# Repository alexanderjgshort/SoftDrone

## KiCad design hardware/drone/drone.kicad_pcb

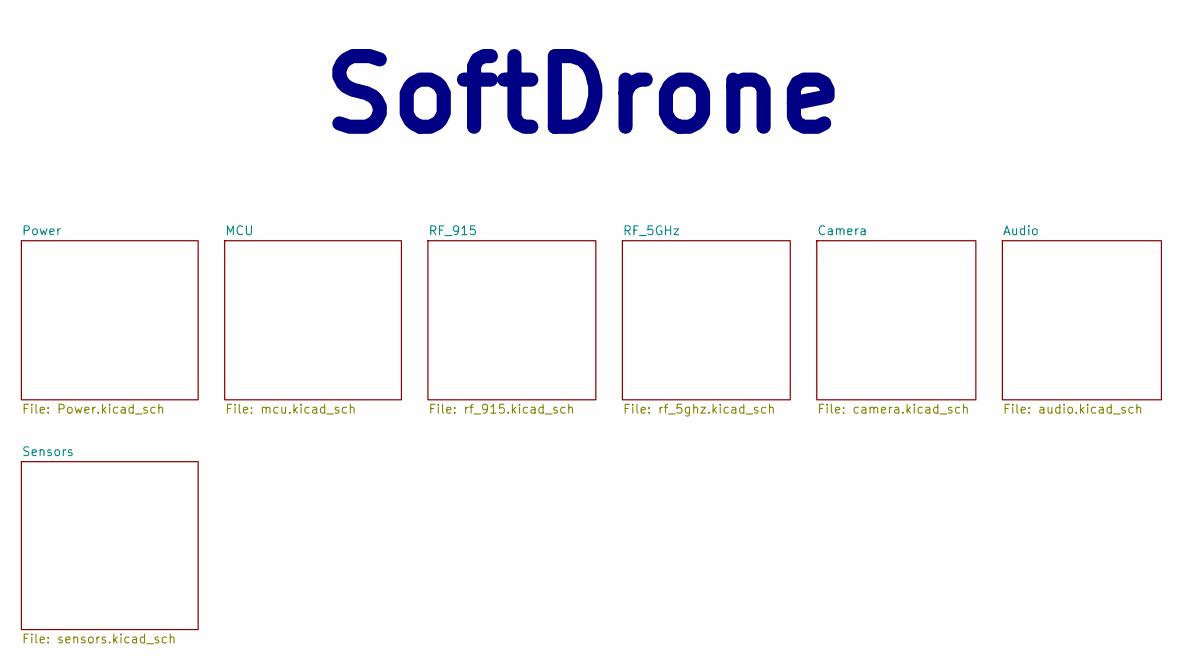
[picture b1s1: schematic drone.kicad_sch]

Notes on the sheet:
SoftDrone

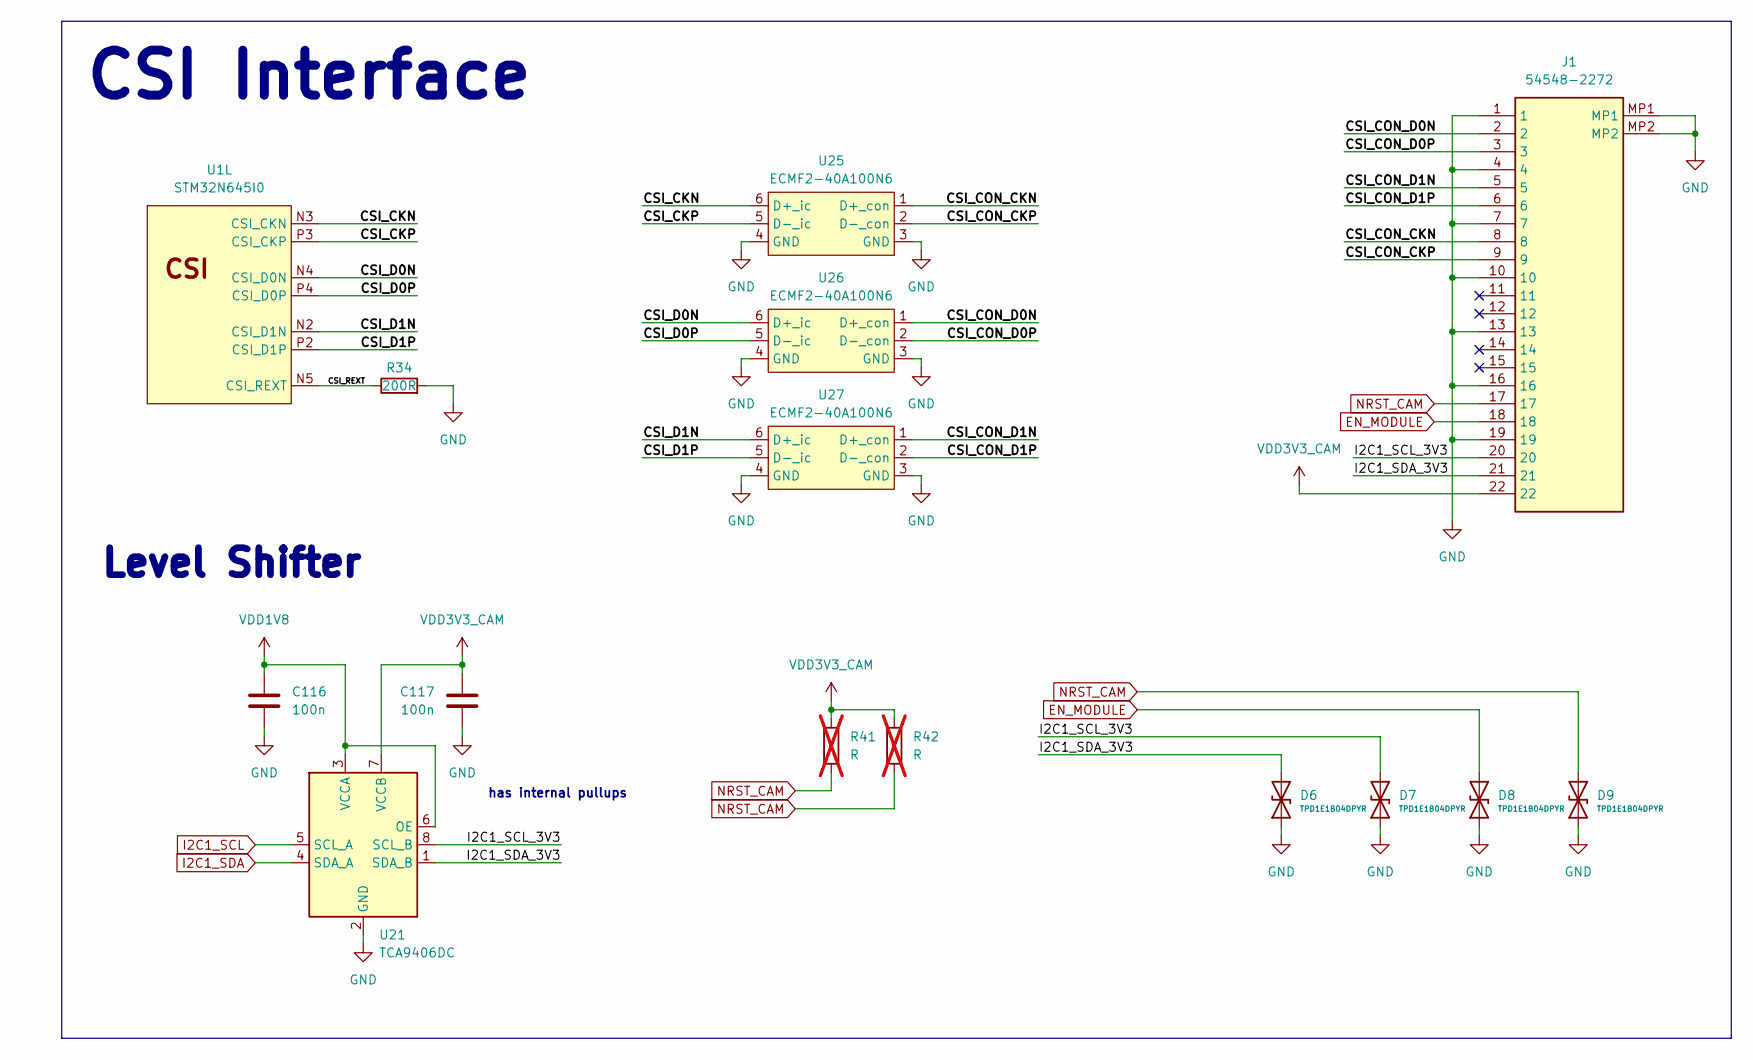
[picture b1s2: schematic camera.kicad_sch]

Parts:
C116, C117: 100n; C_0402_1005Metric
D6, D7, D8, D9: TPD1E1B04DPYR
J1: 54548-2272; 545482272; Manufacturer_Part_Number 54548-2272; Mouser Part Number 538-54548-2272
R34: 200R; R_0402_1005Metric
R41, R42: R; R_0603_1608Metric; not fitted
U1: STM32N645I0; BGA178C80P14X14_1200X1200X100
U21: TCA9406DC; VSSOP-8_2.3x2mm_P0.5mm
U25, U26, U27: ECMF2-40A100N6

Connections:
/Camera/CSI_CKN: U1.N3 (CSI_CKN), U25.6 (D+_ic)
/Camera/CSI_CKP: U1.P3 (CSI_CKP), U25.5 (D-_ic)
/Camera/CSI_CON_CKN: J1.8, U25.1 (D+_con)
/Camera/CSI_CON_CKP: J1.9, U25.2 (D-_con)
/Camera/CSI_CON_D0N: J1.2, U26.1 (D+_con)
/Camera/CSI_CON_D0P: J1.3, U26.2 (D-_con)
/Camera/CSI_CON_D1N: J1.5, U27.1 (D+_con)
/Camera/CSI_CON_D1P: J1.6, U27.2 (D-_con)
/Camera/CSI_D0N: U1.N4 (CSI_D0N), U26.6 (D+_ic)
/Camera/CSI_D0P: U1.P4 (CSI_D0P), U26.5 (D-_ic)
/Camera/CSI_D1N: U1.N2 (CSI_D1N), U27.6 (D+_ic)
/Camera/CSI_D1P: U1.P2 (CSI_D1P), U27.5 (D-_ic)
/Camera/CSI_REXT: R34.1, U1.N5 (CSI_REXT)
/Camera/I2C1_SCL_3V3: D7.2 (A2), J1.20, U21.8 (SCL_B)
/Camera/I2C1_SDA_3V3: D6.2 (A2), J1.21, U21.1 (SDA_B)
EN_MODULE: D8.2 (A2), J1.18; also elsewhere on the board
GND: C116.2, C117.2, D6.1 (A1), D7.1 (A1), D8.1 (A1), D9.1 (A1), J1.1, J1.4, J1.7, J1.10, J1.13, J1.16, J1.19, J1.MP1, J1.MP2, R34.2, U21.2 (GND), U25.3 (GND), U25.4 (GND), U26.3 (GND), U26.4 (GND), U27.3 (GND), U27.4 (GND); also elsewhere on the board
I2C1_SCL: U21.5 (SCL_A); also elsewhere on the board
I2C1_SDA: U21.4 (SDA_A); also elsewhere on the board
NRST_CAM: D9.2 (A2), J1.17, R41.2, R42.2; also elsewhere on the board
VDD1V8: C116.1, U21.3 (VCCA), U21.6 (OE); also elsewhere on the board
VDD3V3_CAM: C117.1, J1.22, R41.1, R42.1, U21.7 (VCCB); also elsewhere on the board

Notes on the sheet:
Level Shifter
has internal pullups
CSI Interface

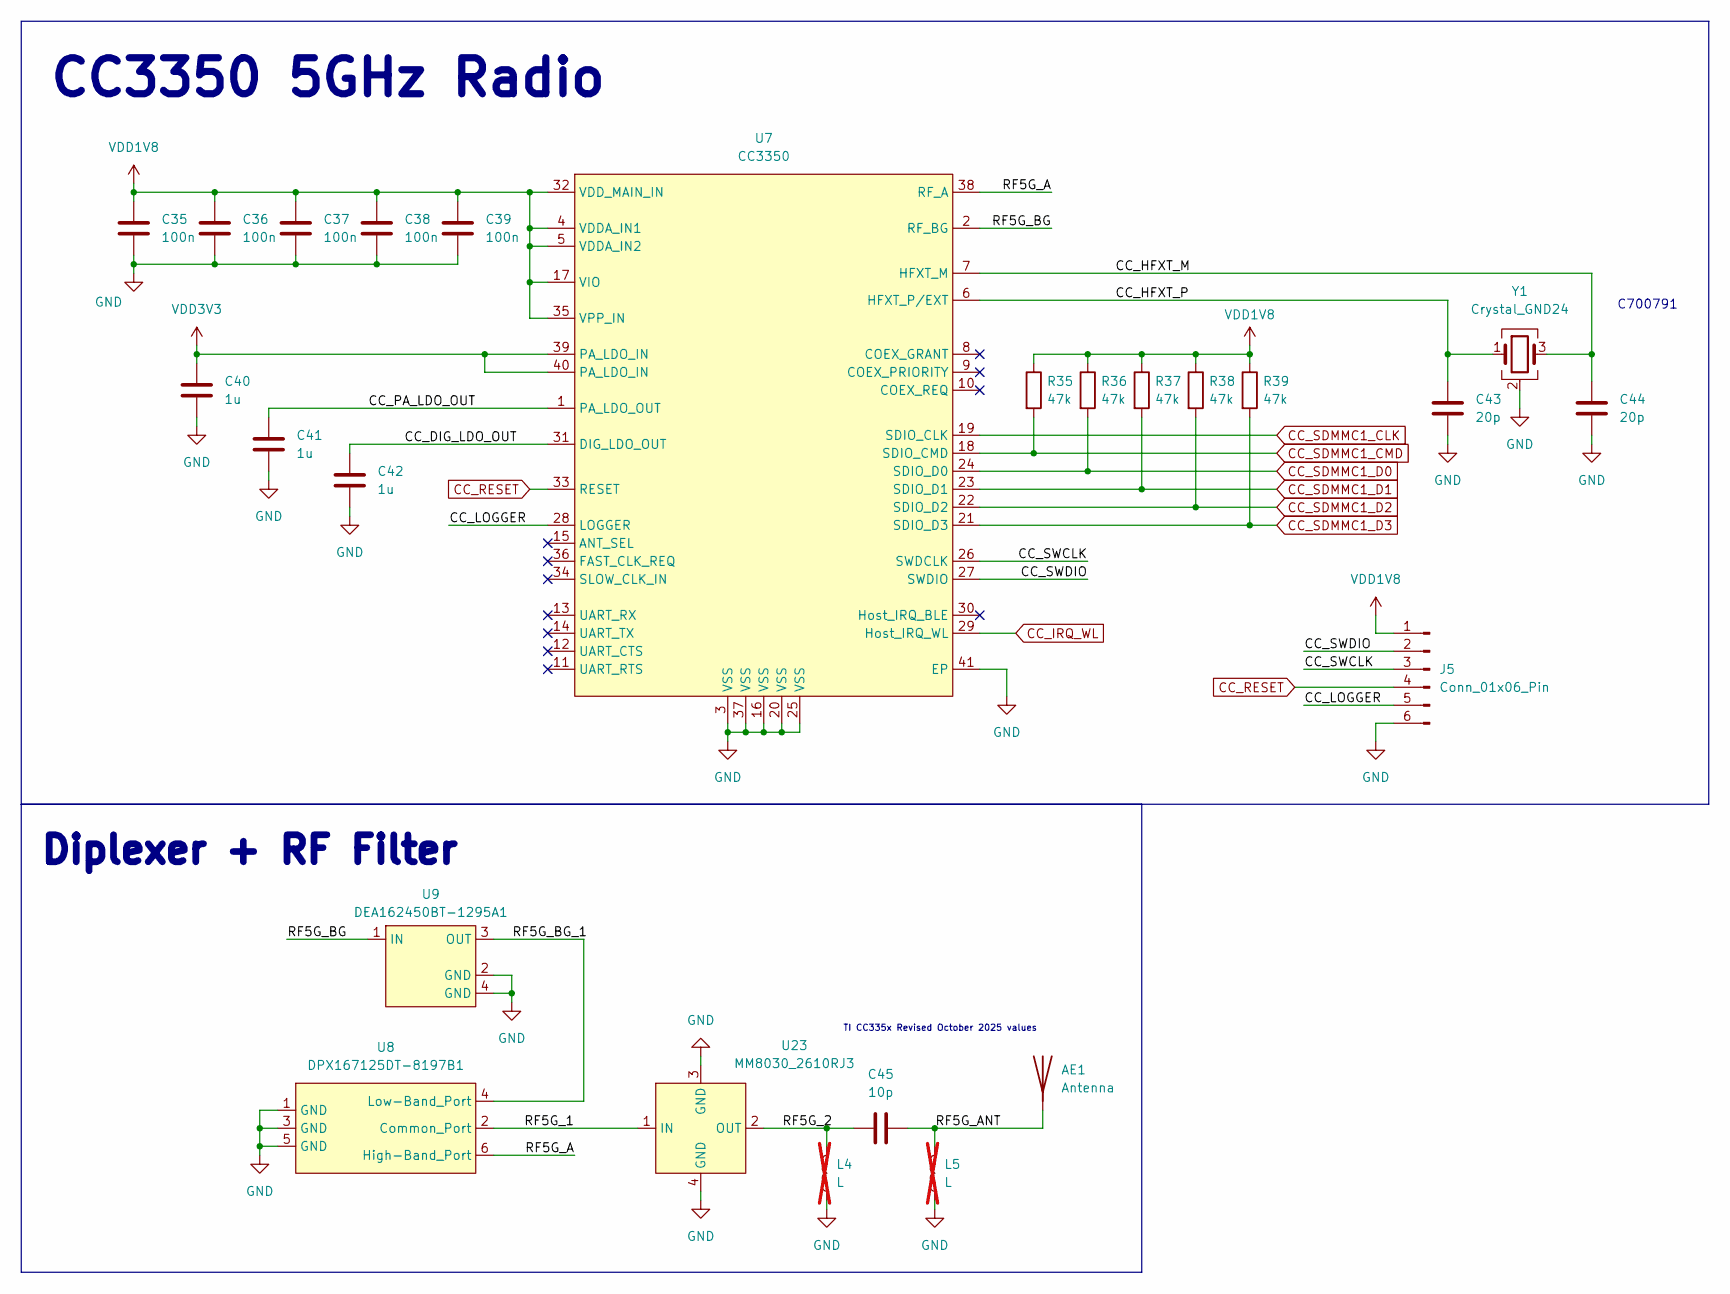
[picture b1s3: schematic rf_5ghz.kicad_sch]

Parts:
AE1: Antenna; ANT-DB1-NSP250-T
C35, C36, C37, C38, C39: 100n; C_0201_0603Metric
C40, C41: 1u; C_0201_0603Metric
C42: 1u; C_0402_1005Metric
C43, C44: 20p; C_0201_0603Metric
C45: 10p; C_0402_1005Metric
J5: Conn_01x06_Pin; PinHeader_1x06_P2.54mm_Vertical
L4, L5: L; L_0402_1005Metric; not fitted
R35, R36, R37, R38, R39: 47k; R_0201_0603Metric
U7: CC3350; QFN40P500X500X80-41N-D
U8: DPX167125DT-8197B1; DPX167125DT8197B1
U9: DEA162450BT-1295A1; DEA162450BT1295A1
U23: MM8030_2610RJ3; MM8030-2610RJ3
Y1: Crystal_GND24; Crystal_SMD_3225-4Pin_3.2x2.5mm

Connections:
/RF_5GHz/CC_DIG_LDO_OUT: C42.1, U7.31 (DIG_LDO_OUT)
/RF_5GHz/CC_HFXT_M: C44.1, U7.7 (HFXT_M), Y1.3
/RF_5GHz/CC_HFXT_P: C43.1, U7.6 (HFXT_P/EXT), Y1.1
/RF_5GHz/CC_LOGGER: J5.5, U7.28 (LOGGER)
/RF_5GHz/CC_PA_LDO_OUT: C41.1, U7.1 (PA_LDO_OUT)
/RF_5GHz/CC_SWCLK: J5.3, U7.26 (SWDCLK)
/RF_5GHz/CC_SWDIO: J5.2, U7.27 (SWDIO)
/RF_5GHz/RF5G_1: U8.2 (Common_Port), U23.1 (IN)
/RF_5GHz/RF5G_2: C45.1, L4.2, U23.2 (OUT)
/RF_5GHz/RF5G_A: U7.38 (RF_A), U8.6 (High-Band_Port)
/RF_5GHz/RF5G_ANT: AE1.1 (A_1), C45.2, L5.2
/RF_5GHz/RF5G_BG: U7.2 (RF_BG), U9.1 (IN)
/RF_5GHz/RF5G_BG_1: U8.4 (Low-Band_Port), U9.3 (OUT)
CC_IRQ_WL: U7.29 (Host_IRQ_WL); also elsewhere on the board
CC_RESET: J5.4, U7.33 (RESET); also elsewhere on the board
CC_SDMMC1_CLK: U7.19 (SDIO_CLK); also elsewhere on the board
CC_SDMMC1_CMD: R35.2, U7.18 (SDIO_CMD); also elsewhere on the board
CC_SDMMC1_D0: R36.2, U7.24 (SDIO_D0); also elsewhere on the board
CC_SDMMC1_D1: R37.2, U7.23 (SDIO_D1); also elsewhere on the board
CC_SDMMC1_D2: R38.2, U7.22 (SDIO_D2); also elsewhere on the board
CC_SDMMC1_D3: R39.2, U7.21 (SDIO_D3); also elsewhere on the board
GND: C35.2, C36.2, C37.2, C38.2, C39.2, C40.2, C41.2, C42.2, C43.2, C44.2, J5.6, L4.1, L5.1, U7.3 (VSS), U7.16 (VSS), U7.20 (VSS), U7.25 (VSS), U7.37 (VSS), U7.41 (EP), U8.1 (GND), U8.3 (GND), U8.5 (GND), U9.2 (GND), U9.4 (GND), U23.3 (GND), U23.4 (GND), Y1.2 (G), Y1.4 (G); also elsewhere on the board
VDD1V8: C35.1, C36.1, C37.1, C38.1, C39.1, J5.1, R35.1, R36.1, R37.1, R38.1, R39.1, U7.4 (VDDA_IN1), U7.5 (VDDA_IN2), U7.17 (VIO), U7.32 (VDD_MAIN_IN), U7.35 (VPP_IN); also elsewhere on the board
VDD3V3: C40.1, U7.39 (PA_LDO_IN), U7.40 (PA_LDO_IN); also elsewhere on the board

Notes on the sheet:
TI CC335x Revised October 2025 values
Diplexer + RF Filter
CC3350 5GHz Radio
C700791

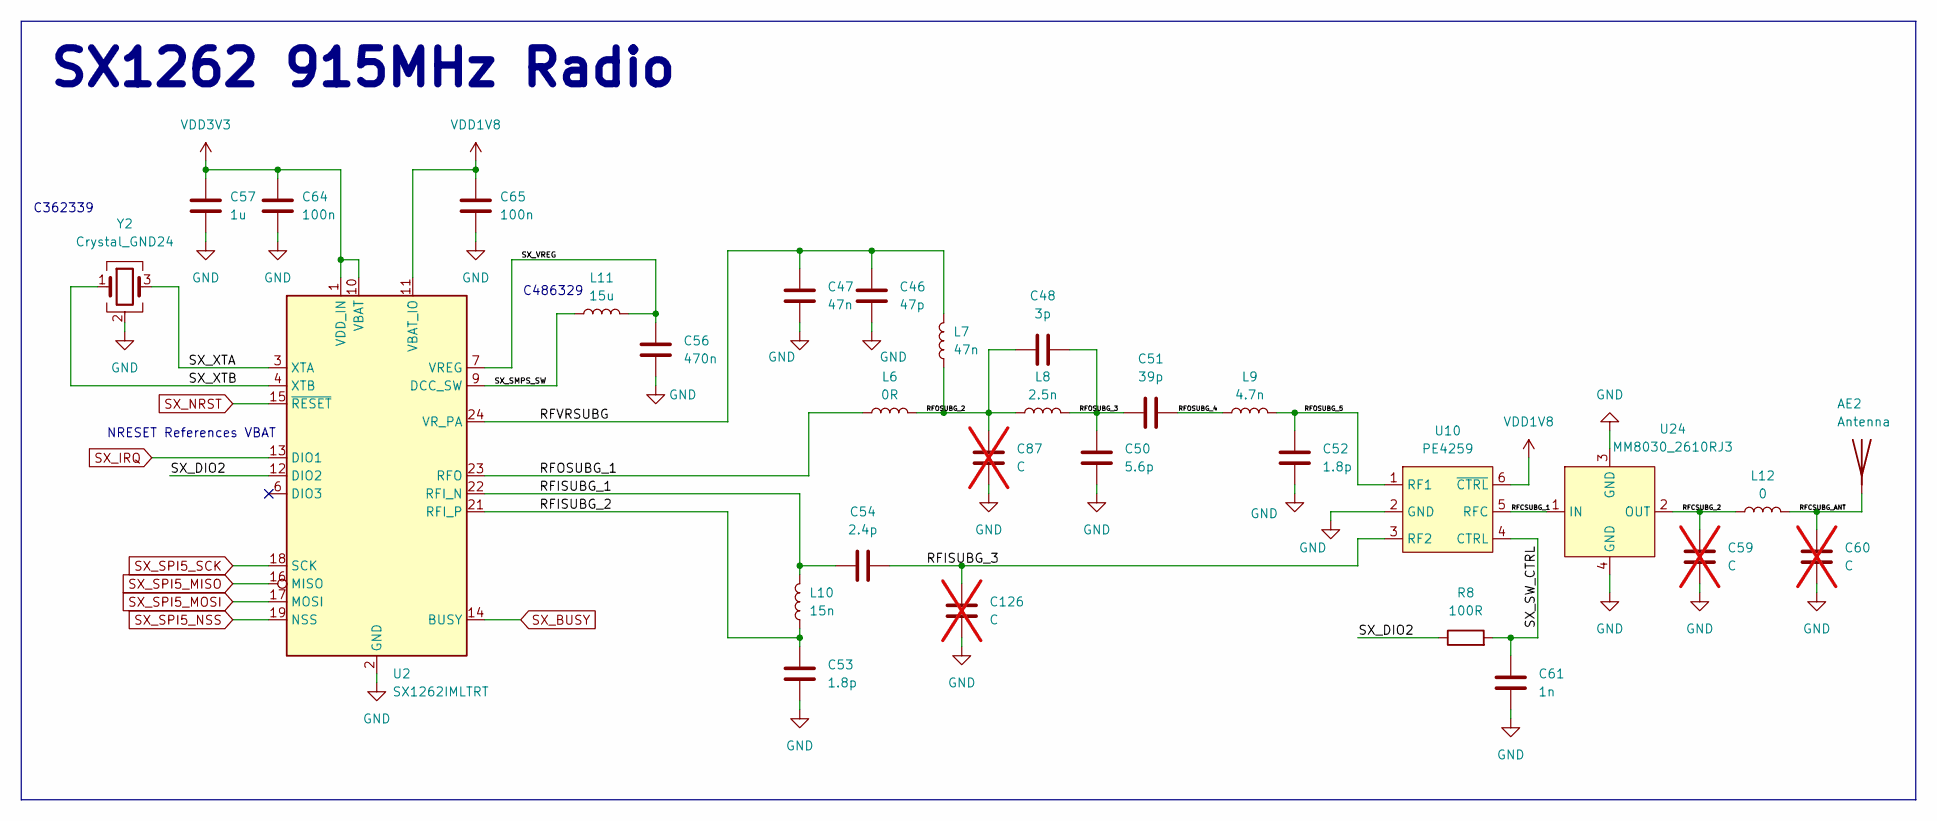
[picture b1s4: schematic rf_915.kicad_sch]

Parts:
AE2: Antenna; ANT916HETH
C46: 47p; C_0402_1005Metric
C47: 47n; C_0402_1005Metric
C48: 3p; C_0402_1005Metric
C50: 5.6p; C_0402_1005Metric
C51: 39p; C_0402_1005Metric
C52, C53: 1.8p; C_0402_1005Metric
C54: 2.4p; C_0402_1005Metric
C56: 470n; C_0402_1005Metric
C57: 1u; C_0201_0603Metric
C59, C60: C; C_0603_1608Metric; not fitted
C61: 1n; C_0402_1005Metric
C64, C65: 100n; C_0201_0603Metric
C87, C126: C; C_0402_1005Metric; not fitted
L6: 0R; L_0402_1005Metric
L7: 47n; L_0402_1005Metric
L8: 2.5n; L_0402_1005Metric
L9: 4.7n; L_0402_1005Metric
L10: 15n; L_0402_1005Metric
L11: 15u; L_0603_1608Metric
L12: 0; L_0603_1608Metric
R8: 100R; R_0402_1005Metric
U2: SX1262IMLTRT; QFN-24-1EP_4x4mm_P0.5mm_EP2.7x2.7mm
U10: PE4259
U24: MM8030_2610RJ3; MM8030-2610RJ3
Y2: Crystal_GND24; Crystal_SMD_3225-4Pin_3.2x2.5mm

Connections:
/RF_915/RFCSUBG_1: U10.5 (RFC), U24.1 (IN)
/RF_915/RFCSUBG_2: C59.2, L12.1, U24.2 (OUT)
/RF_915/RFCSUBG_ANT: AE2.1 (A_1), C60.2, L12.2
/RF_915/RFISUBG_1: C54.2, L10.2, U2.22 (RFI_N)
/RF_915/RFISUBG_2: C53.2, L10.1, U2.21 (RFI_P)
/RF_915/RFISUBG_3: C54.1, C126.1, U10.3 (RF2)
/RF_915/RFOSUBG_1: L6.1, U2.23 (RFO)
/RF_915/RFOSUBG_2: C48.1, C87.1, L6.2, L7.1, L8.1
/RF_915/RFOSUBG_3: C48.2, C50.1, C51.1, L8.2
/RF_915/RFOSUBG_4: C51.2, L9.1
/RF_915/RFOSUBG_5: C52.2, L9.2, U10.1 (RF1)
/RF_915/RFVRSUBG: C46.1, C47.1, L7.2, U2.24 (VR_PA)
/RF_915/SX_DIO2: R8.1, U2.12 (DIO2)
/RF_915/SX_SMPS_SW: L11.1, U2.9 (DCC_SW)
/RF_915/SX_SW_CTRL: C61.2, R8.2, U10.4 (CTRL)
/RF_915/SX_VREG: C56.1, L11.2, U2.7 (VREG)
/RF_915/SX_XTA: U2.3 (XTA), Y2.3
/RF_915/SX_XTB: U2.4 (XTB), Y2.1
GND: C46.2, C47.2, C50.2, C52.1, C53.1, C56.2, C57.2, C59.1, C60.1, C61.1, C64.2, C65.2, C87.2, C126.2, U2.2 (GND), U2.5 (GND), U2.8 (GND), U2.20 (GND), U2.25 (GND), U10.2 (GND), U24.3 (GND), U24.4 (GND), Y2.2 (G), Y2.4 (G); also elsewhere on the board
SX_BUSY: U2.14 (BUSY); also elsewhere on the board
SX_IRQ: U2.13 (DIO1); also elsewhere on the board
SX_NRST: U2.15 (~RESET); also elsewhere on the board
SX_SPI5_MISO: U2.16 (MISO); also elsewhere on the board
SX_SPI5_MOSI: U2.17 (MOSI); also elsewhere on the board
SX_SPI5_NSS: U2.19 (NSS); also elsewhere on the board
SX_SPI5_SCK: U2.18 (SCK); also elsewhere on the board
VDD1V8: C65.1, U2.11 (VBAT_IO), U10.6 (~CTRL); also elsewhere on the board
VDD3V3: C57.1, C64.1, U2.1 (VDD_IN), U2.10 (VBAT); also elsewhere on the board

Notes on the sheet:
SX1262 915MHz Radio
C486329
C362339
NRESET References VBAT

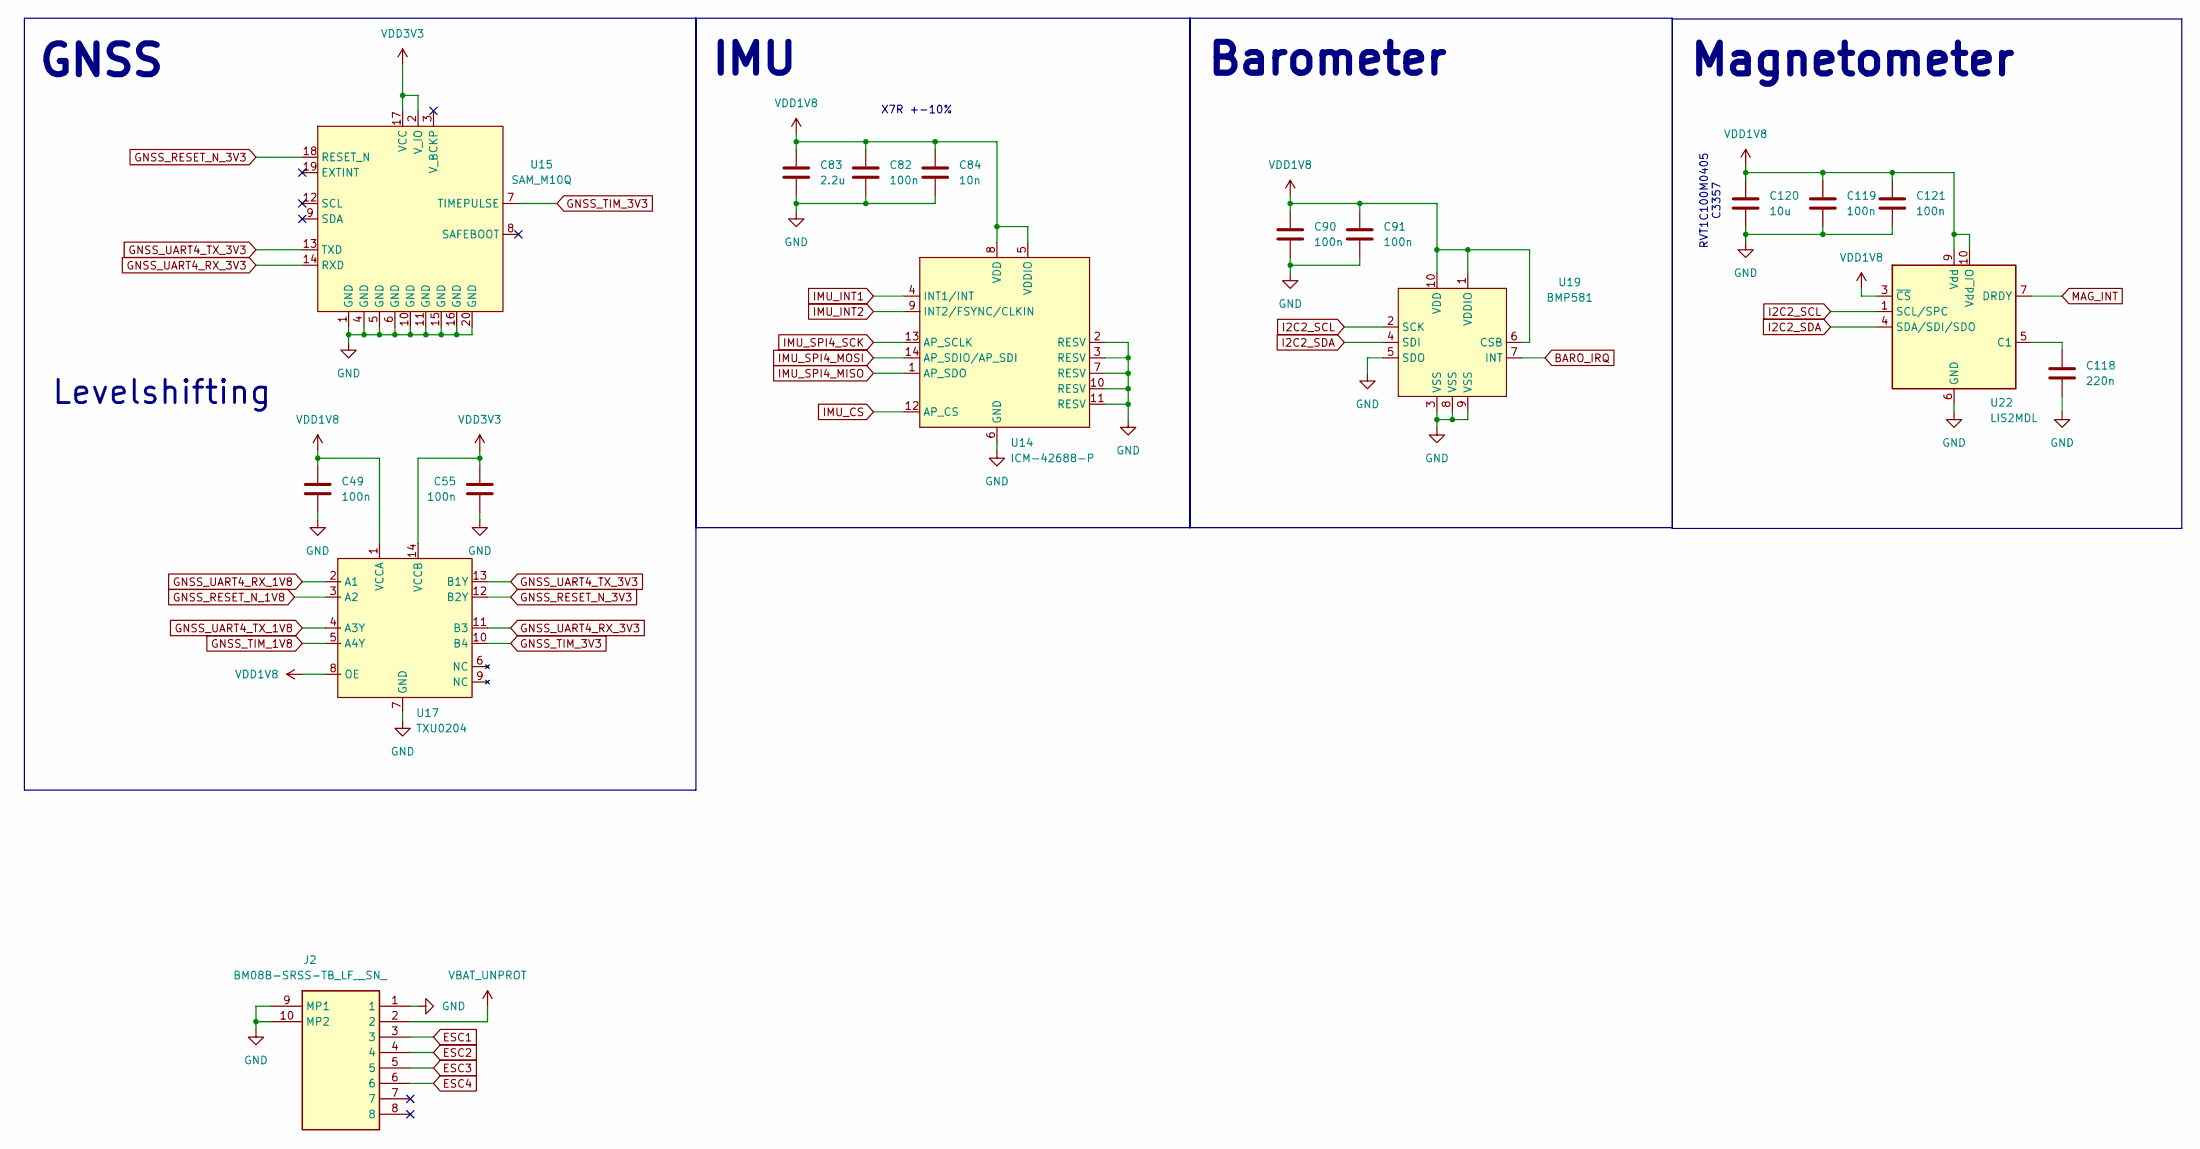
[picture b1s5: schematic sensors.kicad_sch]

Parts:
C49, C55: 100n; C_0402_1005Metric
C82, C90, C91: 100n; C_0201_0603Metric
C83: 2.2u; C_0402_1005Metric
C84: 10n; C_0201_0603Metric
C118: 220n; C_0603_1608Metric
C119, C121: 100n; C_0603_1608Metric
C120: 10u; CP_Elec_4x5.4
J2: BM08B-SRSS-TB_LF__SN_; BM08BSRSSTBLFSN; Manufacturer_Part_Number BM08B-SRSS-TB(LF)(SN); Mouser Part Number N/A
U14: ICM-42688-P; IIM42352
U15: SAM_M10Q; SAMM10Q
U17: TXU0204; TXU0204BQAR
U19: BMP581
U22: LIS2MDL; LGA-12_2x2mm_P0.5mm

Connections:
BARO_IRQ: U19.7 (INT); also elsewhere on the board
ESC1: J2.3; also elsewhere on the board
ESC2: J2.4; also elsewhere on the board
ESC3: J2.5; also elsewhere on the board
ESC4: J2.6; also elsewhere on the board
GND: C49.2, C55.2, C82.2, C83.2, C84.2, C90.2, C91.2, C118.2, C119.2, C120.2, C121.2, J2.1, J2.9 (MP1), J2.10 (MP2), U14.2 (RESV), U14.3 (RESV), U14.6 (GND), U14.7 (RESV), U14.10 (RESV), U14.11 (RESV), U15.1 (GND), U15.4 (GND), U15.5 (GND), U15.6 (GND), U15.10 (GND), U15.11 (GND), U15.15 (GND), U15.16 (GND), U15.20 (GND), U17.7 (GND), U19.3 (VSS), U19.5 (SDO), U19.8 (VSS), U19.9 (VSS), U22.6 (GND), U22.8 (GND); also elsewhere on the board
GNSS_RESET_N_1V8: U17.3 (A2); also elsewhere on the board
GNSS_RESET_N_3V3: U15.18 (RESET_N), U17.12 (B2Y)
GNSS_TIM_1V8: U17.5 (A4Y); also elsewhere on the board
GNSS_TIM_3V3: U15.7 (TIMEPULSE), U17.10 (B4)
GNSS_UART4_RX_1V8: U17.2 (A1); also elsewhere on the board
GNSS_UART4_RX_3V3: U15.14 (RXD), U17.11 (B3)
GNSS_UART4_TX_1V8: U17.4 (A3Y); also elsewhere on the board
GNSS_UART4_TX_3V3: U15.13 (TXD), U17.13 (B1Y)
I2C2_SCL: U19.2 (SCK), U22.1 (SCL/SPC); also elsewhere on the board
I2C2_SDA: U19.4 (SDI), U22.4 (SDA/SDI/SDO); also elsewhere on the board
IMU_CS: U14.12 (AP_CS); also elsewhere on the board
IMU_INT1: U14.4 (INT1/INT); also elsewhere on the board
IMU_INT2: U14.9 (INT2/FSYNC/CLKIN); also elsewhere on the board
IMU_SPI4_MISO: U14.1 (AP_SDO); also elsewhere on the board
IMU_SPI4_MOSI: U14.14 (AP_SDIO/AP_SDI); also elsewhere on the board
IMU_SPI4_SCK: U14.13 (AP_SCLK); also elsewhere on the board
MAG_INT: U22.7 (DRDY); also elsewhere on the board
unnamed: C118.1, U22.5 (C1)
VBAT_UNPROT: J2.2; also elsewhere on the board
VDD1V8: C49.1, C82.1, C83.1, C84.1, C90.1, C91.1, C119.1, C120.1, C121.1, U14.5 (VDDIO), U14.8 (VDD), U17.1 (VCCA), U17.8 (OE), U19.1 (VDDIO), U19.6 (CSB), U19.10 (VDD), U22.3 (~CS), U22.9 (Vdd), U22.10 (Vdd_IO); also elsewhere on the board
VDD3V3: C55.1, U15.2 (V_IO), U15.17 (VCC), U17.14 (VCCB); also elsewhere on the board

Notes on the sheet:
Levelshifting
X7R +-10%
IMU
RVT1C100M0405 C3357
Barometer
GNSS
Magnetometer

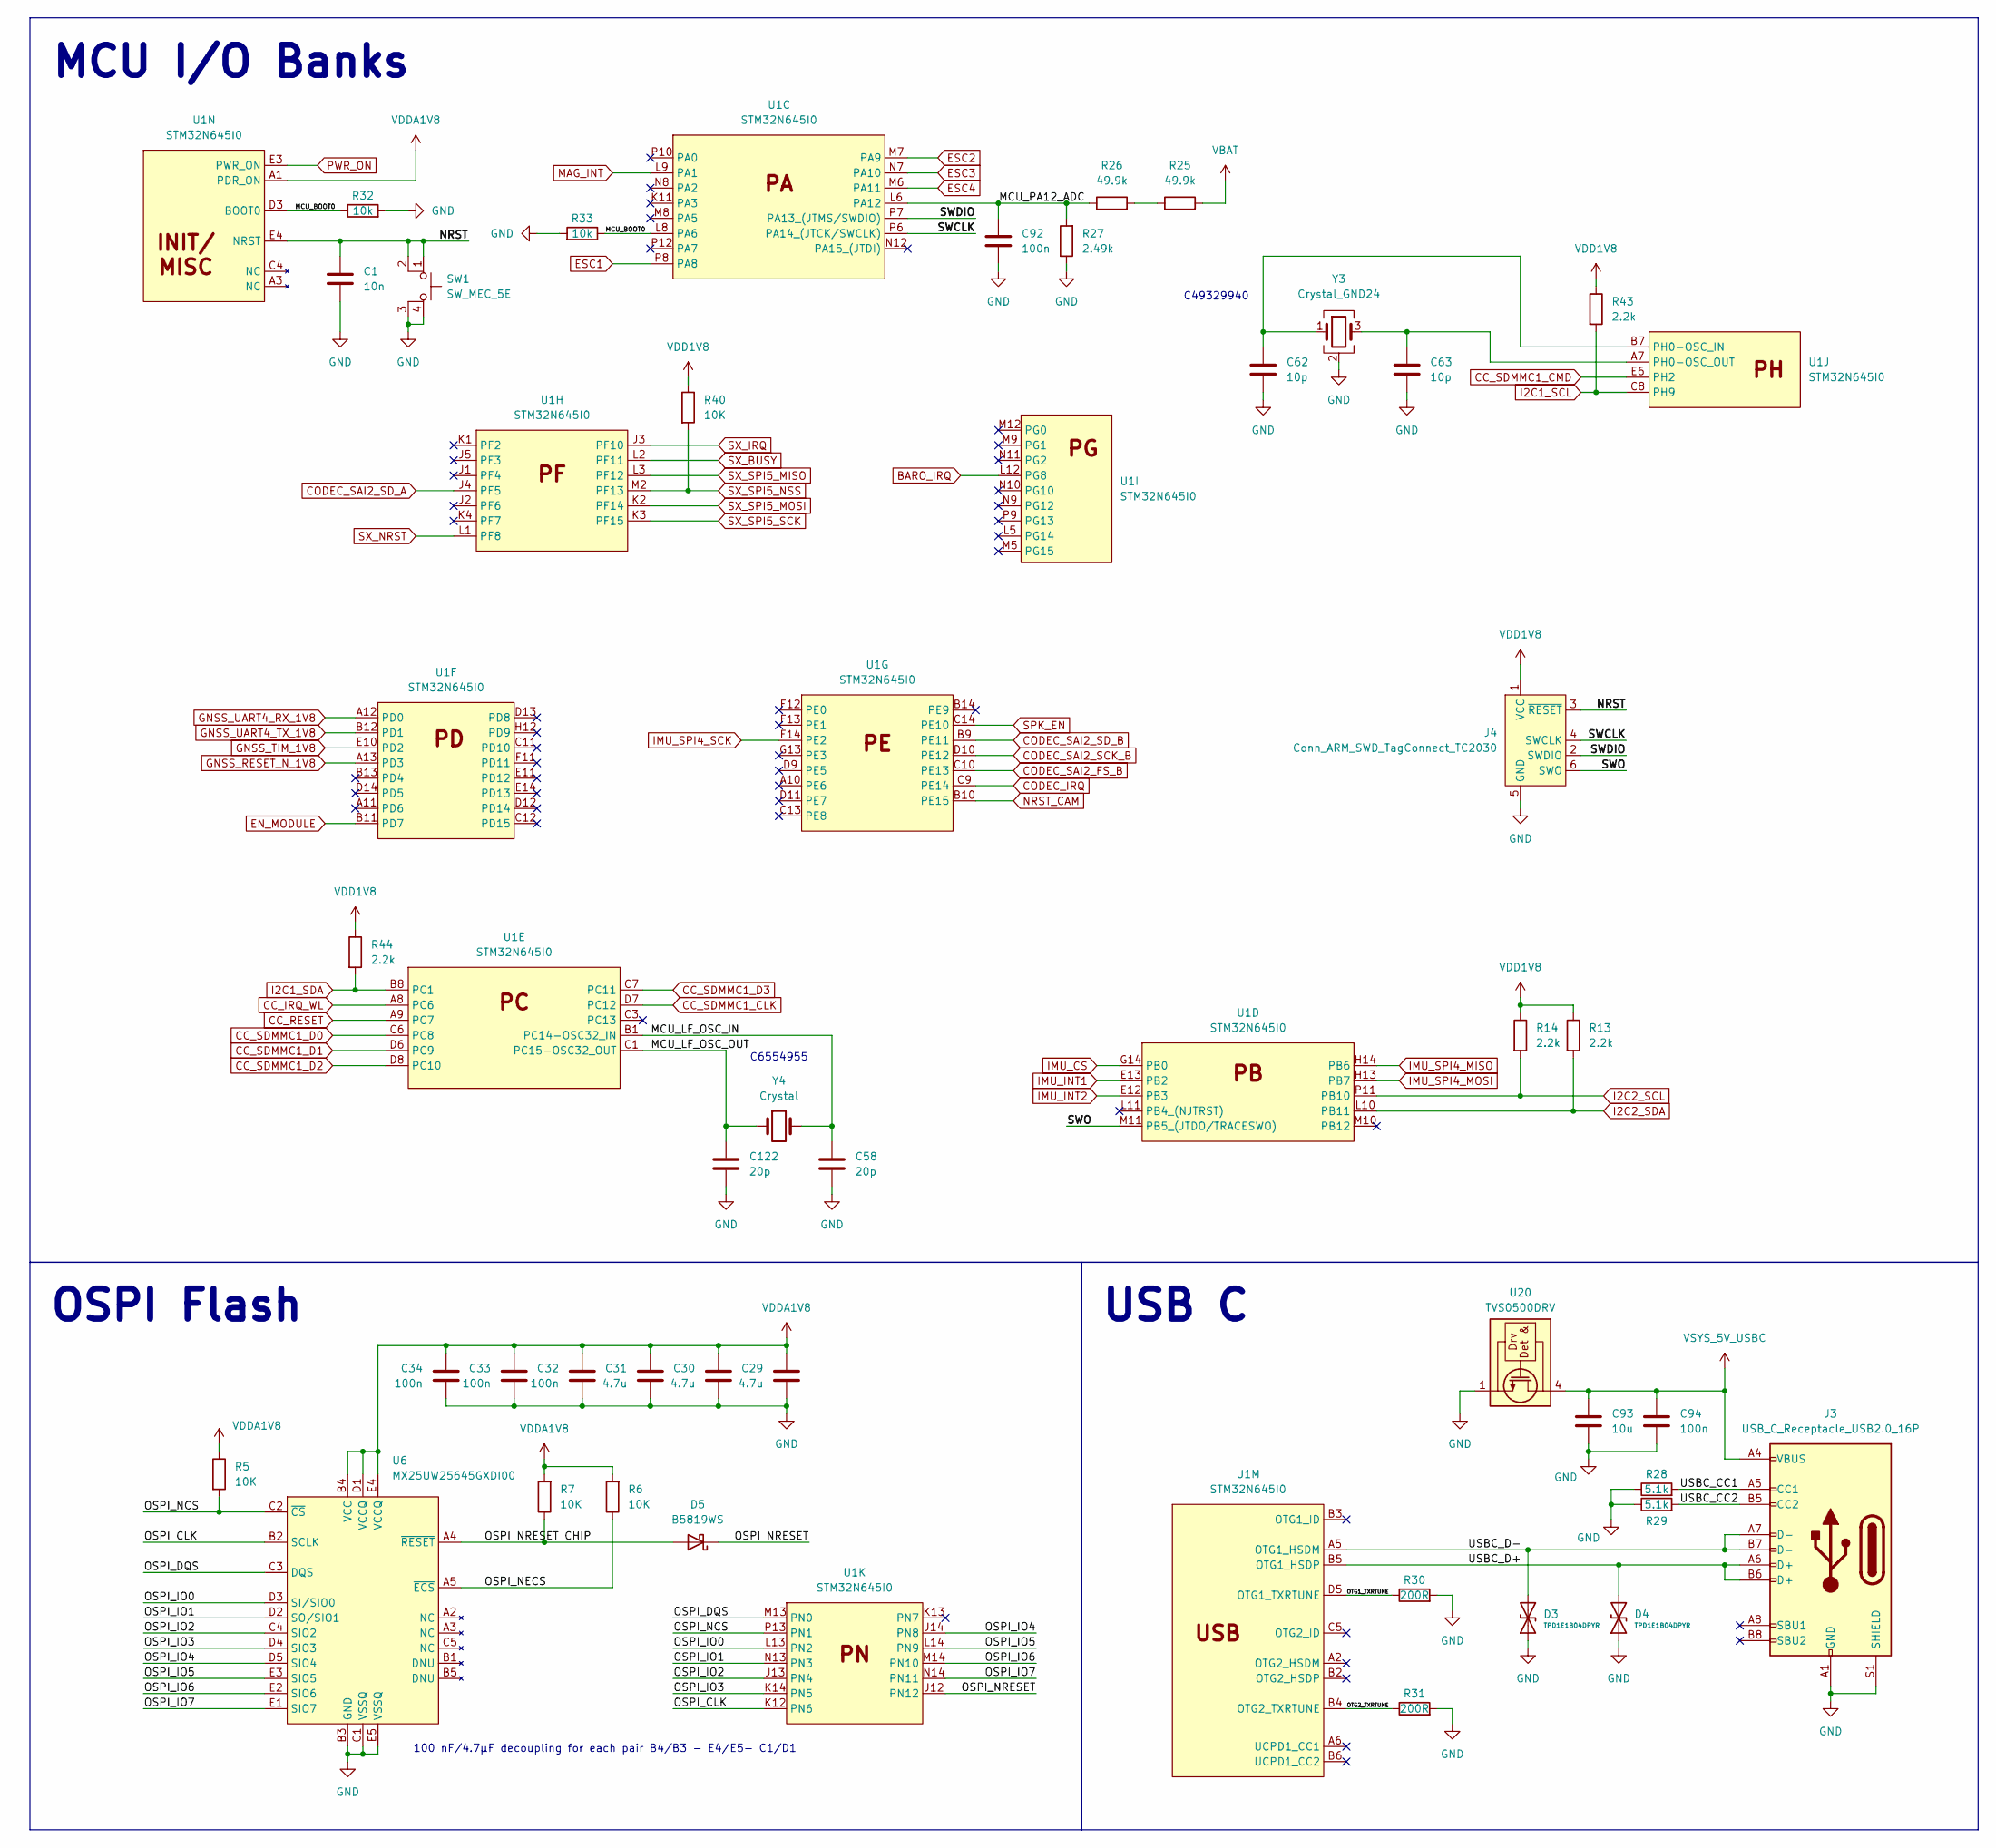
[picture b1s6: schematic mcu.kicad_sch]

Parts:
C1: 10n; C_0402_1005Metric
C29, C30, C31: 4.7u; C_0603_1608Metric
C32, C33, C34, C94: 100n; C_0402_1005Metric
C58, C122: 20p; C_0201_0603Metric
C62, C63: 10p; C_0201_0603Metric
C92: 100n; C_0603_1608Metric
C93: 10u; C_0805_2012Metric
D3, D4: TPD1E1B04DPYR
D5: B5819WS; D_SOD-323
J3: USB_C_Receptacle_USB2.0_16P; USB_C_Receptacle_HRO_TYPE-C-31-M-12
J4: Conn_ARM_SWD_TagConnect_TC2030; Tag-Connect_TC2030-IDC-FP_2x03_P1.27mm_Vertical
R5, R6, R7, R40: 10K; R_0402_1005Metric
R13, R14, R43, R44: 2.2k; R_0402_1005Metric
R25, R26: 49.9k; R_0603_1608Metric
R27: 2.49k; R_0603_1608Metric
R28, R29: 5.1k; R_0402_1005Metric
R30, R31: 200R; R_0402_1005Metric
R32, R33: 10k; R_0402_1005Metric
SW1: SW_MEC_5E; 1825910-6
U1: STM32N645I0; BGA178C80P14X14_1200X1200X100
U6: MX25UW25645GXDI00; BGA24C100P5X5_600X800X120
U20: TVS0500DRV; WSON-6-1EP_2x2mm_P0.65mm_EP1x1.6mm
Y3: Crystal_GND24; XTM32048000NT00351001
Y4: Crystal; FC-135R 32.7680KA-A3

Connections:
/MCU/MCU_BOOT0: R32.1, R33.1, U1.D3 (BOOT0), U1.L8 (PA6)
/MCU/MCU_LF_OSC_IN: C58.1, U1.B1 (PC14-OSC32_IN), Y4.2
/MCU/MCU_LF_OSC_OUT: C122.1, U1.C1 (PC15-OSC32_OUT), Y4.1
/MCU/MCU_PA12_ADC: C92.1, R26.1, R27.2, U1.L6 (PA12)
/MCU/NRST: C1.1, J4.3 (~RESET), SW1.1, SW1.2, U1.E4 (NRST)
/MCU/OSPI_CLK: U1.K12 (PN6), U6.B2 (SCLK)
/MCU/OSPI_DQS: U1.M13 (PN0), U6.C3 (DQS)
/MCU/OSPI_IO0: U1.L13 (PN2), U6.D3 (SI/SIO0)
/MCU/OSPI_IO1: U1.N13 (PN3), U6.D2 (SO/SIO1)
/MCU/OSPI_IO2: U1.J13 (PN4), U6.C4 (SIO2)
/MCU/OSPI_IO3: U1.K14 (PN5), U6.D4 (SIO3)
/MCU/OSPI_IO4: U1.J14 (PN8), U6.D5 (SIO4)
/MCU/OSPI_IO5: U1.L14 (PN9), U6.E3 (SIO5)
/MCU/OSPI_IO6: U1.M14 (PN10), U6.E2 (SIO6)
/MCU/OSPI_IO7: U1.N14 (PN11), U6.E1 (SIO7)
/MCU/OSPI_NCS: R5.2, U1.P13 (PN1), U6.C2 (~CS)
/MCU/OSPI_NECS: R6.1, U6.A5 (~ECS)
/MCU/OSPI_NRESET: D5.1 (K), U1.J12 (PN12)
/MCU/OSPI_NRESET_CHIP: D5.2 (A), R7.1, U6.A4 (~RESET)
/MCU/OTG1_TXRTUNE: R30.1, U1.D5 (OTG1_TXRTUNE)
/MCU/OTG2_TXRTUNE: R31.1, U1.B4 (OTG2_TXRTUNE)
/MCU/SWCLK: J4.4 (SWCLK), U1.P6 (PA14_(JTCK/SWCLK))
/MCU/SWDIO: J4.2 (SWDIO), U1.P7 (PA13_(JTMS/SWDIO))
/MCU/SWO: J4.6 (SWO), U1.M11 (PB5_(JTDO/TRACESWO))
/MCU/USBC_CC1: J3.A5 (CC1), R28.2
/MCU/USBC_CC2: J3.B5 (CC2), R29.2
/MCU/USBC_D+: D4.2 (A2), J3.A6 (D+), J3.B6 (D+), U1.B5 (OTG1_HSDP)
/MCU/USBC_D-: D3.2 (A2), J3.A7 (D-), J3.B7 (D-), U1.A5 (OTG1_HSDM)
BARO_IRQ: U1.L12 (PG8); also elsewhere on the board
CC_IRQ_WL: U1.A8 (PC6); also elsewhere on the board
CC_RESET: U1.A9 (PC7); also elsewhere on the board
CC_SDMMC1_CLK: U1.D7 (PC12); also elsewhere on the board
CC_SDMMC1_CMD: U1.E6 (PH2); also elsewhere on the board
CC_SDMMC1_D0: U1.C6 (PC8); also elsewhere on the board
CC_SDMMC1_D1: U1.D6 (PC9); also elsewhere on the board
CC_SDMMC1_D2: U1.D8 (PC10); also elsewhere on the board
CC_SDMMC1_D3: U1.C7 (PC11); also elsewhere on the board
CODEC_IRQ: U1.C9 (PE14); also elsewhere on the board
CODEC_SAI2_FS_B: U1.C10 (PE13); also elsewhere on the board
CODEC_SAI2_SCK_B: U1.D10 (PE12); also elsewhere on the board
CODEC_SAI2_SD_A: U1.J4 (PF5); also elsewhere on the board
CODEC_SAI2_SD_B: U1.B9 (PE11); also elsewhere on the board
EN_MODULE: U1.B11 (PD7); also elsewhere on the board
ESC1: U1.P8 (PA8); also elsewhere on the board
ESC2: U1.M7 (PA9); also elsewhere on the board
ESC3: U1.N7 (PA10); also elsewhere on the board
ESC4: U1.M6 (PA11); also elsewhere on the board
GND: C1.2, C29.2, C30.2, C31.2, C32.2, C33.2, C34.2, C58.2, C62.2, C63.2, C92.2, C93.2, C94.2, C122.2, D3.1 (A1), D4.1 (A1), J3.A1 (GND), J3.A12 (GND), J3.B1 (GND), J3.B12 (GND), J3.S1 (SHIELD), J4.5 (GND), R27.1, R28.1, R29.1, R30.2, R31.2, R32.2, R33.2, SW1.3 (K), SW1.4 (A), U6.B3 (GND), U6.C1 (VSSQ), U6.E5 (VSSQ), U20.1 (GND), U20.2 (GND), U20.3 (GND), U20.7 (GND), Y3.2 (G), Y3.4 (G); also elsewhere on the board
GNSS_RESET_N_1V8: U1.A13 (PD3); also elsewhere on the board
GNSS_TIM_1V8: U1.E10 (PD2); also elsewhere on the board
GNSS_UART4_RX_1V8: U1.A12 (PD0); also elsewhere on the board
GNSS_UART4_TX_1V8: U1.B12 (PD1); also elsewhere on the board
I2C1_SCL: R43.2, U1.C8 (PH9); also elsewhere on the board
I2C1_SDA: R44.2, U1.B8 (PC1); also elsewhere on the board
I2C2_SCL: R14.2, U1.P11 (PB10); also elsewhere on the board
I2C2_SDA: R13.2, U1.L10 (PB11); also elsewhere on the board
IMU_CS: U1.G14 (PB0); also elsewhere on the board
IMU_INT1: U1.E13 (PB2); also elsewhere on the board
IMU_INT2: U1.E12 (PB3); also elsewhere on the board
IMU_SPI4_MISO: U1.H14 (PB6); also elsewhere on the board
IMU_SPI4_MOSI: U1.H13 (PB7); also elsewhere on the board
IMU_SPI4_SCK: U1.F14 (PE2); also elsewhere on the board
MAG_INT: U1.L9 (PA1); also elsewhere on the board
NRST_CAM: U1.B10 (PE15); also elsewhere on the board
unnamed: R25.1, R26.2
unnamed: C62.1, U1.B7 (PH0-OSC_IN), Y3.1
unnamed: C63.1, U1.A7 (PH0-OSC_OUT), Y3.3
PWR_ON: U1.E3 (PWR_ON); also elsewhere on the board
SPK_EN: U1.C14 (PE10); also elsewhere on the board
SX_BUSY: U1.L2 (PF11); also elsewhere on the board
SX_IRQ: U1.J3 (PF10); also elsewhere on the board
SX_NRST: U1.L1 (PF8); also elsewhere on the board
SX_SPI5_MISO: U1.L3 (PF12); also elsewhere on the board
SX_SPI5_MOSI: U1.K2 (PF14); also elsewhere on the board
SX_SPI5_NSS: R40.2, U1.M2 (PF13); also elsewhere on the board
SX_SPI5_SCK: U1.K3 (PF15); also elsewhere on the board
VBAT: R25.2; also elsewhere on the board
VDD1V8: J4.1 (VCC), R13.1, R14.1, R40.1, R43.1, R44.1; also elsewhere on the board
VDDA1V8: C29.1, C30.1, C31.1, C32.1, C33.1, C34.1, R5.1, R6.2, R7.2, U1.A1 (PDR_ON), U6.B4 (VCC), U6.D1 (VCCQ), U6.E4 (VCCQ); also elsewhere on the board
VSYS_5V_USBC: C93.1, C94.1, J3.A4 (VBUS), J3.A9 (VBUS), J3.B4 (VBUS), J3.B9 (VBUS), U20.4 (IN), U20.5 (IN), U20.6 (IN); also elsewhere on the board

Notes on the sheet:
MCU I/O Banks
OSPI Flash
USB C
100 nF/4.7μF decoupling for each pair B4/B3 - E4/E5- C1/D1
C49329940
C6554955
